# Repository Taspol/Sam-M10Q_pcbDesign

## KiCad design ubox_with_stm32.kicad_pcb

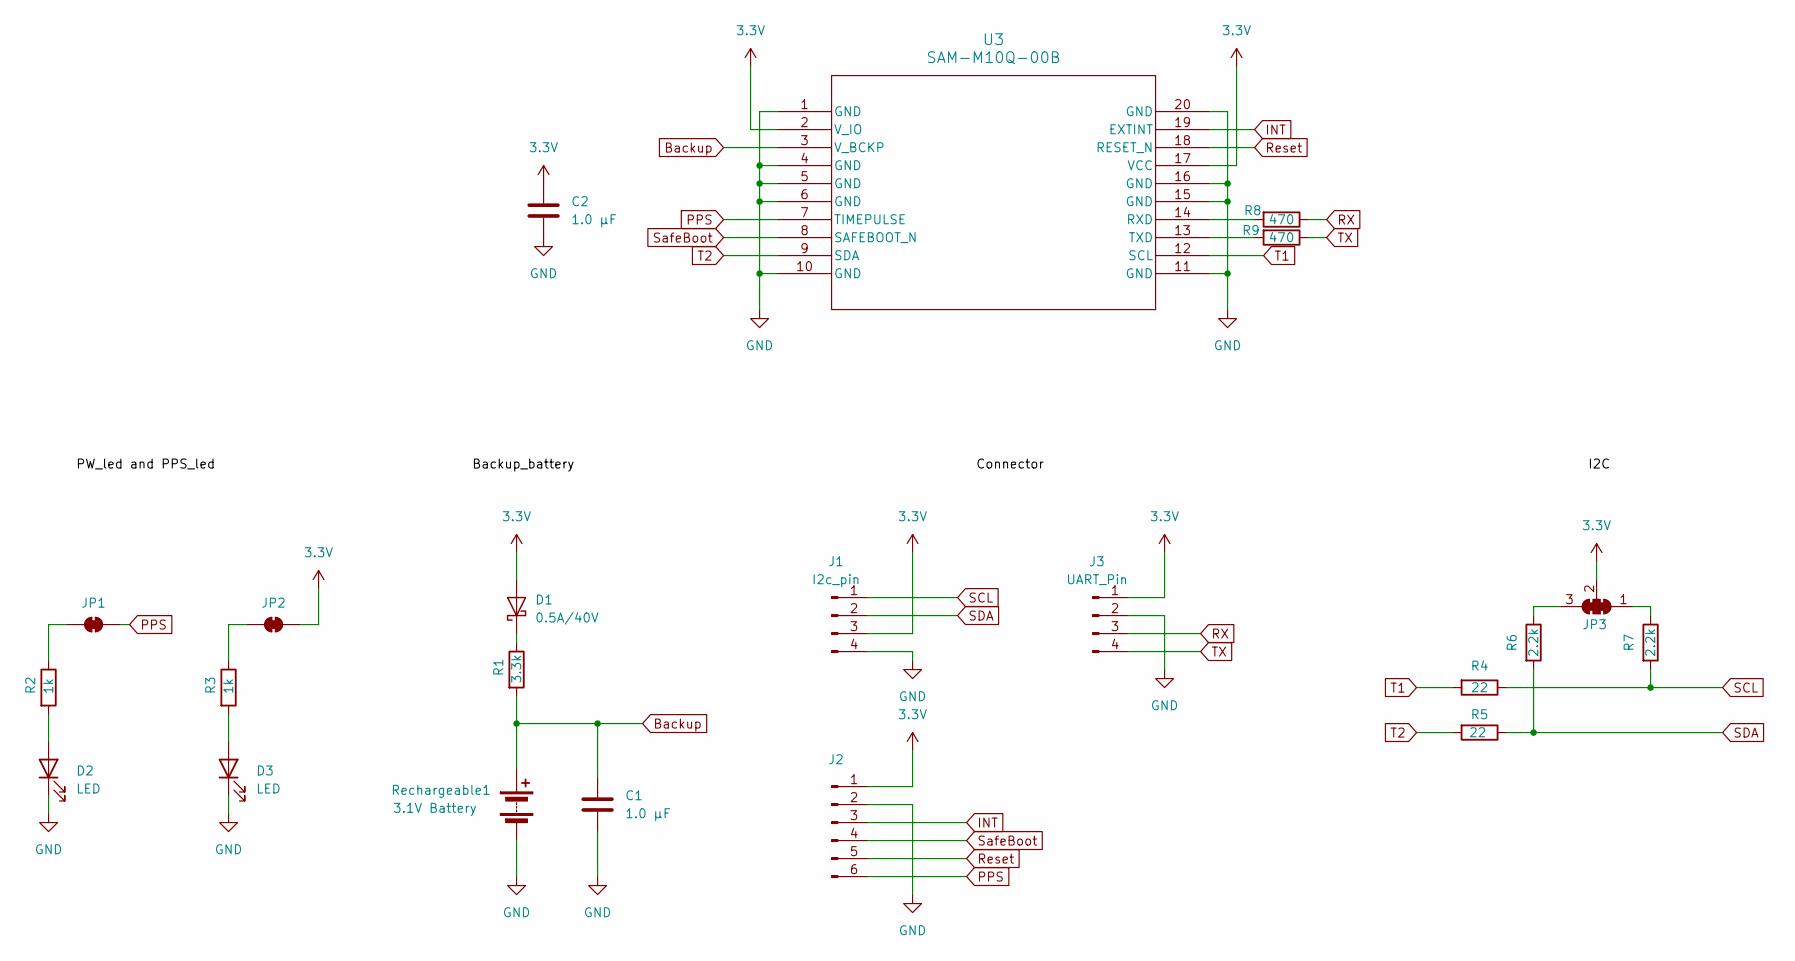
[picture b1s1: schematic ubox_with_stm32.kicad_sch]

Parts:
C1, C2: 1.0 µF; C_0201_0603Metric
D1: 0.5A/40V; D_SOD-123F
D2, D3: LED; LED_0402_1005Metric
J1: I2c_pin; PinHeader_1x04_P1.00mm_Horizontal
J2: PinHeader_1x06_P1.00mm_Horizontal
J3: UART_Pin; PinHeader_1x04_P1.00mm_Horizontal
JP1: SolderJumper_2_Bridged; SolderJumper-2_P1.3mm_Open_Pad1.0x1.5mm
JP2: SolderJumper-2_P1.3mm_Open_Pad1.0x1.5mm
JP3: SolderJumper_3_Bridged123; SolderJumper-3_P1.3mm_Open_Pad1.0x1.5mm_NumberLabels
R1: 3.3k; R_0201_0603Metric
R2, R3: 1k; R_0201_0603Metric
R4, R5: 22; R_0201_0603Metric
R6, R7: 2.2k; R_0201_0603Metric
R8, R9: 470; R_0201_0603Metric
Rechargeable1: 3.1V Battery; BatteryHolder_Seiko_MS621F
U3: SAM-M10Q-00B; SAM-M10Q_UBL

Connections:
3.3V: C2.1, D1.2 (A), J1.3, J2.1, J3.1, JP2.2 (B), JP3.2 (C), U3.2 (V_IO), U3.17 (VCC)
Backup: C1.1, R1.2, Rechargeable1.1 (+), U3.3 (V_BCKP)
GND: C1.2, C2.2, D2.1 (K), D3.1 (K), J1.4, J2.2, J3.2, Rechargeable1.2 (-), U3.1 (GND), U3.4 (GND), U3.5 (GND), U3.6 (GND), U3.10 (GND), U3.11 (GND), U3.15 (GND), U3.16 (GND), U3.20 (GND)
INT: J2.3, U3.19 (EXTINT)
unnamed: D1.1 (K), R1.1
unnamed: D2.2 (A), R2.2
unnamed: D3.2 (A), R3.2
unnamed: JP1.1 (A), R2.1
unnamed: JP2.1 (A), R3.1
unnamed: JP3.1 (A), R7.1
unnamed: JP3.3 (B), R6.1
unnamed: R8.2, U3.14 (RXD)
unnamed: R9.2, U3.13 (TXD)
PPS: J2.6, JP1.2 (B), U3.7 (TIMEPULSE)
RX: J3.3, R8.1
Reset: J2.5, U3.18 (RESET_N)
SCL: J1.1, R4.1, R7.2
SDA: J1.2, R5.1, R6.2
SafeBoot: J2.4, U3.8 (SAFEBOOT_N)
T1: R4.2, U3.12 (SCL)
T2: R5.2, U3.9 (SDA)
TX: J3.4, R9.1

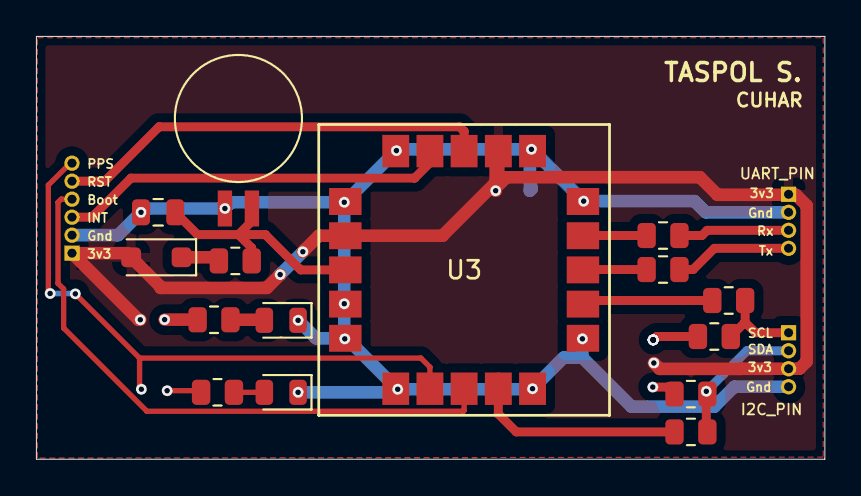
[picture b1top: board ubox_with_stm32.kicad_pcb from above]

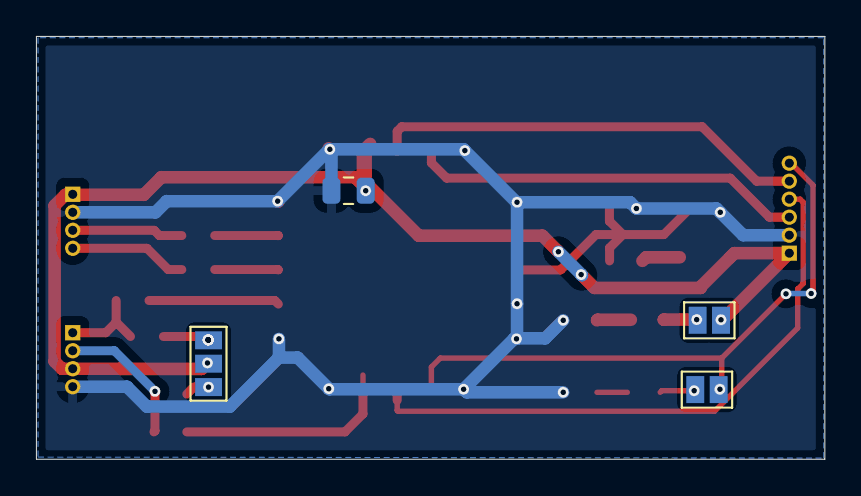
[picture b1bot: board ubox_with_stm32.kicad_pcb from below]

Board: 2 copper layers, 43.8 x 23.5 mm, 22 parts (7 on the bottom side), 22 nets.

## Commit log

2024-12-14 init repo
2024-12-14 add gitignore
2024-12-14 remove backupfolder
2024-12-16 add decoupling
2024-12-24 resize component
2025-01-07 compatible with breadboard
2025-01-07 compatible with bread board
2025-01-08 feat: add fabrication & silkscreen
